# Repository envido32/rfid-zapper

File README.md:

# RFID Zapper

RFID Zapper sirve para quemar, dejando fuera de funcionamiento de forma irreversible los chips tipo RFID como el que se encuentran en llaves de puertas electronicas, [tarjetas de transporte público](https://www.sube.gob.ar/), [pasaportes](https://www.digitalcourage.de/), [boletas de voto electrónico](https://youtu.be/bJT6KLP6tWA), etc. No deja marca visible en absoluto ni emite ruido alguno. 

Este dispositivo debe utilizarse SOLO con fines didácticos o de pruebas. El mal uso del mismo **puede ocasionar serios daños en dispositivos electrónicos.**

**ATENCIÓN! Este dispositivo tiene una salida en ALTO VOLTAJE. Puede ocasionar daños en el organismo o incluso la muerte si se aplica la descarga sobre el cuerpo. Debe manipularse adecuadamente. No utilizar sin protección adecuada.**

## Licencia

RFID Zapper es un proyecto libre realizado por [*Manolo Envido*](https://twitter.com/Envido32), basado en el diseño presentado en la serie de videos de [*The Post Apocalyptic Inventor*](https://www.youtube.com/watch?v=E_Nsf0uU8IY&list=PLxaGnte1Dq0my2dtPL5y8sPR7xYXRrOCb).

Libre para utilizar, modificar, compartir y demás bajo los términos de la licencia [CERN Open Hardware Licence v1.2](LICENSE).

## Principio de funcionamiento

Se trata de un circuito elevador de tensión alimentado por una batería alcalina de 9v. Este elevador carga el capacitor y luego al cerrar el segundo interruptor se descarga el capacitor a través de la antena RFID. Esto genera un pulso electromagnético que al ser captado por un chip RFID lo utilizara como alimentación. Al ser un pulso de alta intensidad (y corta duración) la energía absorbida por el chip sera más alta que la soportada por el integrado probocándole un daño irreparable de forma totalmente silenciosa e invisible.

El circuito elevador de tensión es del tipo [boost](https://en.wikipedia.org/wiki/Boost_converter) alimentado por una [batería alcalina de 9v](https://en.wikipedia.org/wiki/Nine-volt_battery). Este circuito es controlado por un [PWM](https://en.wikipedia.org/wiki/Pulse-width_modulation) básico realizado con el [Timer 555](https://en.wikipedia.org/wiki/555_timer_IC) y controlado por el potenciómetro, se recomienda evitar un ciclo de trabajo del PWM mayor al 50% para evitar daños a la batería. Una vez cargado el capacitor el circuito de feedback enciende el LED y desactiva el Timer 555.

## Lite Edition

Menos componentes, más compacto. 

***Made with KiCAD***

***Order in PCBWay***

## Lista de materiales

Description | Part | References | Value | Footprint | Quantity Per PCB
---- | ---- | ---- | ---- | ---- | ---- 
Bornier | 2x1 | SW_SPST1 SW_SPST2 BT1 | SW_CHARGE SW_ZAP Baterry9v | Bornier | 3
Switch | DPDT | SW_SPST1 SW_SPST2 | SW_CHARGE SW_ZAP | Bornier | 1
Battery Cell | Baterry9v | BT1 | Alkaline 9v | Bornier | 1
Timer 555 IC | NE555 | U1 | NE555 | DIP 8 W7.62mm | 1
Capacitor | Ceramic | C1 | 100nF | Disc 4.3mm W1.9mm P5.00mm | 1
Capacitor | Ceramic | C2 | 10nF | Disc 4.3mm W1.9mm P5.00mm | 1
Capacitor | Polarised | C3 | 120uF 400v | Radial D18.0mm P7.50mm | 1
LED | Generic | DL1 | Any colour | LED 3.0mm | 1
Diode | Ultra Fast Recovery Rectifier | D3 | RG4 | P10.16mm | 1
Diode | Generic | D1 D2 | 1N4148 | P10.16mm | 2
Diode | Zenner v5.1 | DZ1 | 1N4733A | P10.16mm | 1
PowerMESH MOSFET | N-CHANNEL 900V 4ohm 3.5 A | Q2 | P3NB90 FP IRF3205| TO-220 | 1
Inductor | With Iron Core | L1 | 100uH | Toroid 5x10mm | 1
Small Signal Transistor | NPN 45V Vce 0.1A Ic | Q1 | BC549 | TO-92 | 1
Resistor | Generic | R1 R6 | 330ohm 1/8w | L3.6mm D1.6mm P7.62mm | 2
Resistor | Generic | R3 R9 | 150kohm 1/8w | L3.6mm D1.6mm P7.62mm | 2
Resistor | Generic | R8 | 10Mohm 1/8w | L3.6mm D1.6mm P7.62mm | 1
Potentionmeter | Trimmer | R2 | 500kohm 1/8w | POT | 1

Costo de los materiales total aproximado (a Septiembre 2017, argentina): 
*10 U$D*

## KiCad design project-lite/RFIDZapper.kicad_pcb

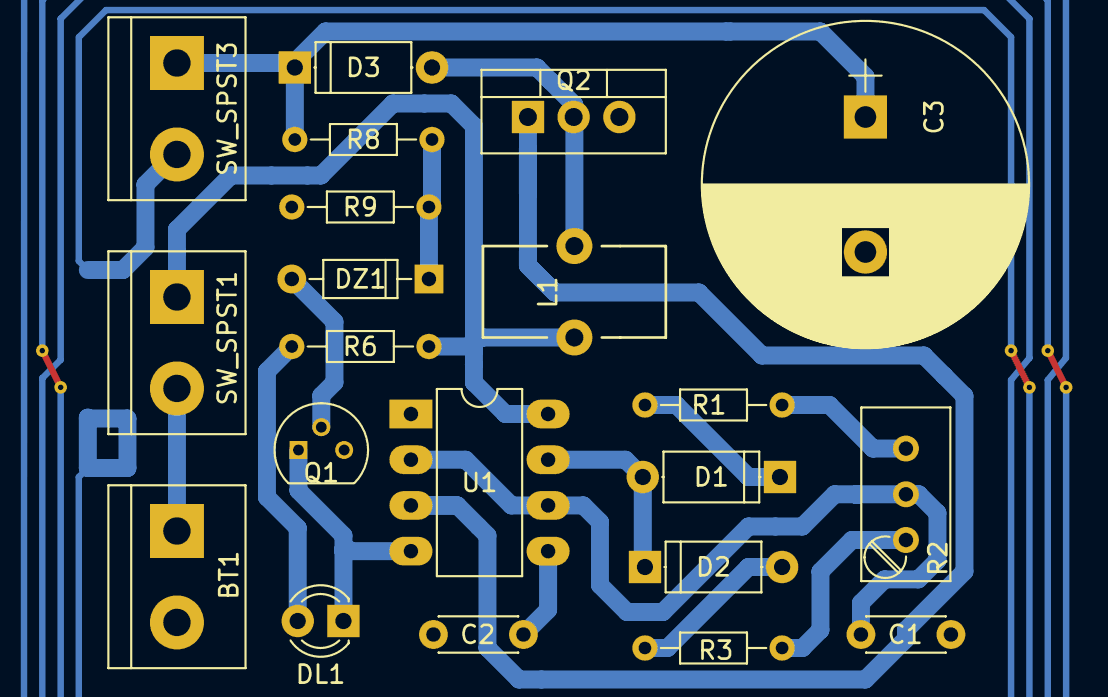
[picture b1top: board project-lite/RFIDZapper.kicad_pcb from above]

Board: 2 copper layers, 22 parts (1 on the bottom side), 18 nets.

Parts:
AE1: Antenna_RFID; NFC_ANTENNA2_INSIDE_CONNECTION
BT1: Battery9v; bornier2
C1: 100nF; C_Disc_D4.3mm_W1.9mm_P5.00mm
C2: 10nF; C_Disc_D4.3mm_W1.9mm_P5.00mm
C3: 120uF 400v; CP_Radial_D18.0mm_P7.50mm
D1, D2: 1N4148; D_A-405_P7.62mm_Horizontal
D3: RG4; D_A-405_P7.62mm_Horizontal
DL1: LED; LED_D3.0mm
DZ1: 5.1v; D_DO-35_SOD27_P7.62mm_Horizontal
L1: 100uH; Choke_Toroid_5x10mm_Vertical
Q1: BC549; TO-92_Molded_Narrow
Q2: P3NB90 FP; TO-220_Vertical
R1, R6: 330; R_Axial_DIN0204_L3.6mm_D1.6mm_P7.62mm_Horizontal
R2: 500k; Potentiometer_Trimmer_Bourns_3296W
R3, R9: 150k; R_Axial_DIN0204_L3.6mm_D1.6mm_P7.62mm_Horizontal
R8: 10M; R_Axial_DIN0204_L3.6mm_D1.6mm_P7.62mm_Horizontal
SW_SPST1: SW_CHARGE; bornier2
SW_SPST3: SW_ZAP; bornier2
U1: NE555; DIP-8_W7.62mm_LongPads

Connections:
/CV: C2.1, U1.5
/DIS: D1.2, D2.1, U1.7
/THR: C1.2, R2.2, U1.2, U1.6
/VCC: BT1.1, SW_SPST1.2
/VHI: C3.1, D3.1, R8.1, SW_SPST3.1
/VLO: L1.1, R6.1, SW_SPST1.1, U1.8
GNDPWR: AE1.2, BT1.2, C1.1, C2.2, C3.2, Q1.3, Q2.3, R9.2, U1.1
unnamed: AE1.1, SW_SPST3.2
unnamed: D1.1, R1.1
unnamed: D2.2, R3.1
unnamed: D3.2, L1.2, Q2.2
unnamed: DL1.2, R6.2
unnamed: DZ1.1, R8.2, R9.1
unnamed: DZ1.2, Q1.2
unnamed: R1.2, R2.3
unnamed: R2.1, R3.2
PWM: Q2.1, U1.3
RST: DL1.1, Q1.1, U1.4

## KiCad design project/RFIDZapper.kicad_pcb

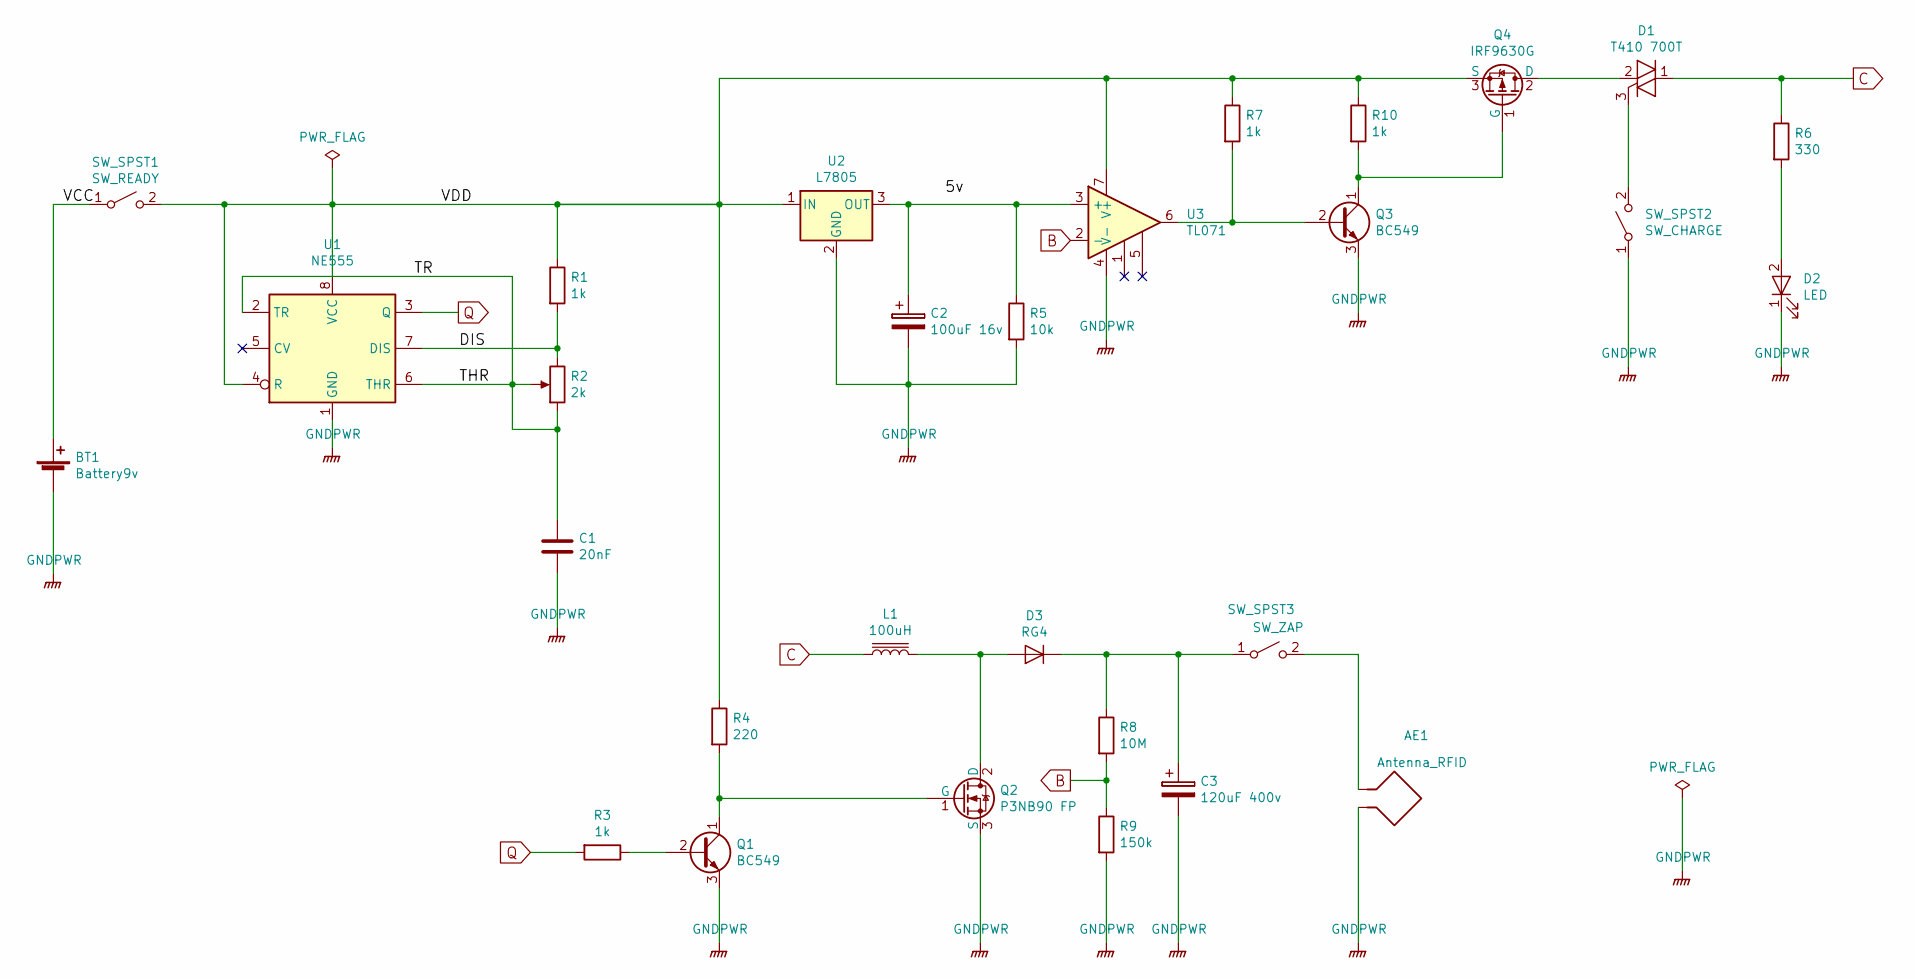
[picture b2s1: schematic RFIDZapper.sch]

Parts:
AE1: Antenna_RFID; NFC_ANTENNA_40_40
BT1: Battery9v; bornier2
C1: 20nF; C_Disc_D4.3mm_W1.9mm_P5.00mm
C2: 100uF 16v; CP_Radial_D4.0mm_P2.00mm
C3: 120uF 400v; CP_Radial_D18.0mm_P7.50mm
D1: T410 700T; TO-220_Horizontal
D2: LED; LED_D3.0mm
D3: RG4; D_A-405_P10.16mm_Horizontal
L1: 100uH; Choke_Toroid_5x10mm_Vertical
Q1, Q3: BC549; TO-92_Molded_Narrow
Q2: P3NB90 FP; TO-220_Horizontal
Q4: IRF9630G; TO-220_Horizontal
R1, R3, R7, R10: 1k; R_Axial_DIN0204_L3.6mm_D1.6mm_P7.62mm_Horizontal
R2: 2k; Potentiometer_Trimmer_Bourns_3296W
R4: 220; R_Axial_DIN0204_L3.6mm_D1.6mm_P7.62mm_Horizontal
R5: 10k; R_Axial_DIN0204_L3.6mm_D1.6mm_P7.62mm_Horizontal
R6: 330; R_Axial_DIN0204_L3.6mm_D1.6mm_P7.62mm_Horizontal
R8: 10M; R_Axial_DIN0204_L3.6mm_D1.6mm_P7.62mm_Horizontal
R9: 150k; R_Axial_DIN0204_L3.6mm_D1.6mm_P7.62mm_Horizontal
SW_SPST1: SW_READY; bornier2
SW_SPST2: SW_CHARGE; bornier2
SW_SPST3: SW_ZAP; bornier2
U1: NE555; DIP-8_W7.62mm_LongPads
U2: L7805; TO-220_Horizontal
U3: TL071; DIP-8_W7.62mm_LongPads

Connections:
/DIS: R1.2, R2.3, U1.7 (DIS)
/THR: C1.1, R2.1, R2.2, U1.2 (TR), U1.6 (THR)
/VCC: BT1.1 (+), SW_SPST1.1 (A)
/VDD: Q4.3 (S), R1.1, R4.1, R7.1, R10.1, SW_SPST1.2 (B), U1.4 (R), U1.8 (VCC), U2.1 (IN), U3.7 (V+)
A: Q1.1 (C), Q2.1 (G), R4.2
B: R8.2, R9.1, U3.2 (-)
C: D1.2 (A2), Q4.2 (D)
GNDPWR: AE1.2, BT1.2 (-), C1.2, C2.2, C3.2, D2.1 (K), Q1.3 (E), Q2.3 (S), Q3.3 (E), R5.2, R9.2, SW_SPST2.1 (A), U1.1 (GND), U2.2 (GND), U3.4 (V-)
unnamed: AE1.1, SW_SPST3.2 (B)
unnamed: C2.1, R5.1, U2.3 (OUT), U3.3 (+)
unnamed: C3.1, D3.1 (K), R8.1, SW_SPST3.1 (A)
unnamed: D1.1 (A1), L1.1, R6.1
unnamed: D1.3 (G), SW_SPST2.2 (B)
unnamed: D2.2 (A), R6.2
unnamed: D3.2 (A), L1.2, Q2.2 (D)
unnamed: Q1.2 (B), R3.1
unnamed: Q3.1 (C), Q4.1 (G), R10.2
unnamed: Q3.2 (B), R7.2, U3.6
Q: R3.2, U1.3 (Q)

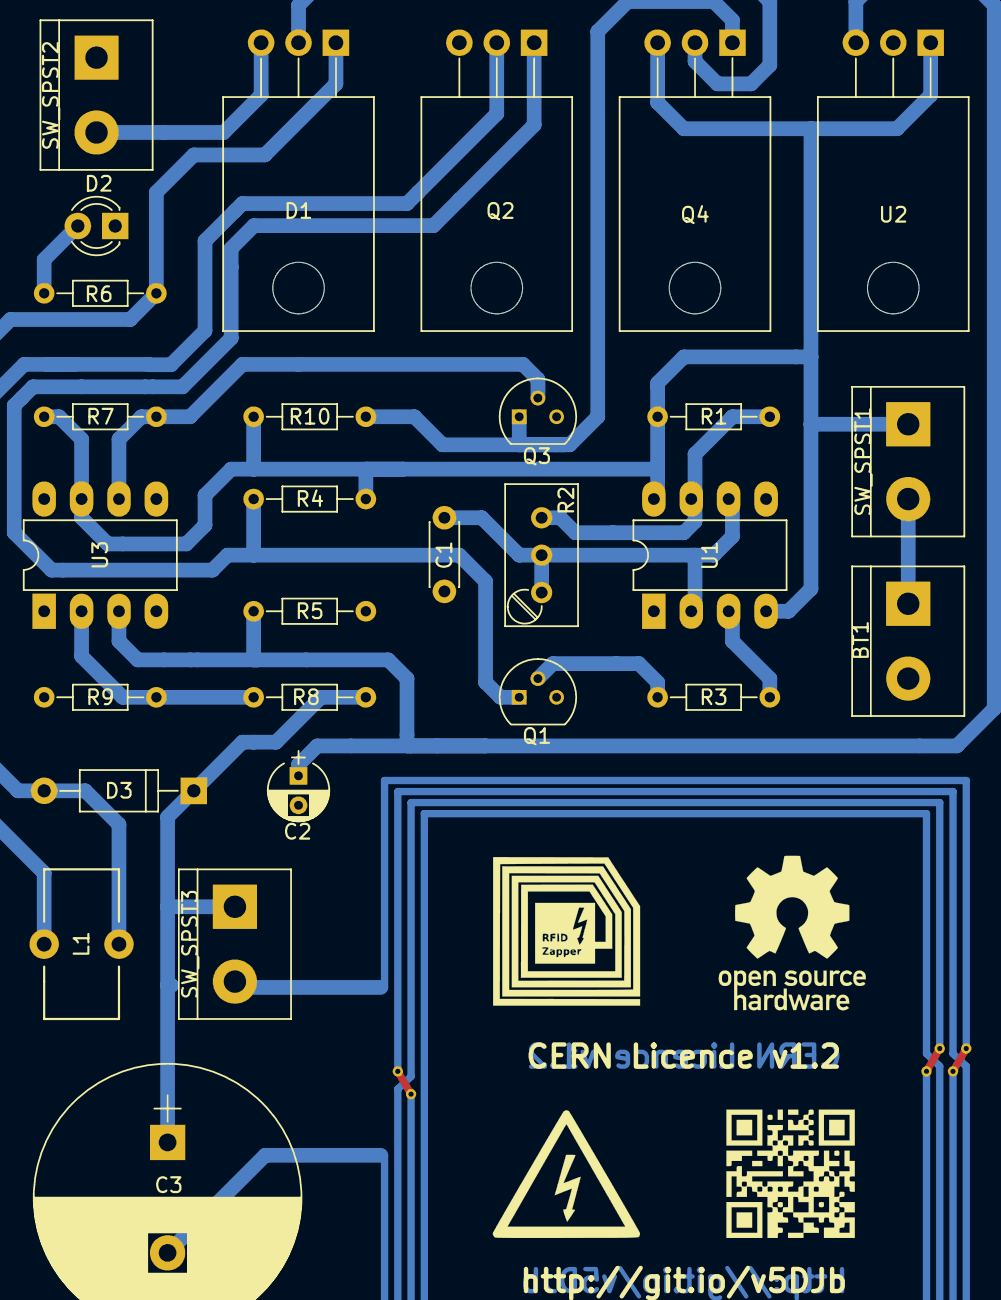
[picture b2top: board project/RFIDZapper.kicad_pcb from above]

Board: 2 copper layers, 29 parts (1 on the bottom side), 19 nets.

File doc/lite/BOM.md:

## RFIF Zapper ( http://git.io/v5DJb ) 

## Lista de materiales

Description | Part | References | Value | Footprint | Quantity Per PCB
---- | ---- | ---- | ---- | ---- | ---- 
single battery cell | Battery_Cell | BT1 | Battery9v | bornier2 | 1
Polarised capacitor | CP | C2 | 100uF 16v | CP_Radial_D4.0mm_P2.00mm | 1
Polarised capacitor | CP | C3 | 120uF 400v | CP_Radial_D18.0mm_P7.50mm | 1
Unpolarized capacitor | C | C1 | 20nF | C_Disc_D4.3mm_W1.9mm_P5.00mm | 1
LED generic | LED | D2 | LED | LED_D3.0mm | 1
Diode | D | D3 | RG4 | D_A-405_P10.16mm_Horizontal | 1
triode for alternating current (TRIAC) | Q_TRIAC_AAG | D1 | T410 700T | TO-220_Horizontal | 1
Inductor with Iron Core | L_Core_Iron | L1 | 100uH | Choke_Toroid_5x10mm_Vertical | 1
45V Vce, 0.1A Ic, NPN, Small Signal Transistor, TO-92 | BC549 | Q1 Q3 | BC549 | TO-92_Molded_Narrow | 2
6.5A, 200V, 0.800 Ohm, P-Channel Power MOSFET | IRF9540N-RESCUE-RFIDZapper | Q4 | IRF9630G | TO-220_Horizontal | 1
N - CHANNEL 900V - 4 ohm - 3.5 A PowerMESH MOSFET | IRF3205 | Q2 | P3NB90 FP | TO-220_Horizontal | 1
Resistor | R | R8 | 10M | R_Axial_DIN0204_L3.6mm_D1.6mm_P7.62mm_Horizontal | 1
Resistor | R | R5 | 10k | R_Axial_DIN0204_L3.6mm_D1.6mm_P7.62mm_Horizontal | 1
Resistor | R | R9 | 150k | R_Axial_DIN0204_L3.6mm_D1.6mm_P7.62mm_Horizontal | 1
Resistor | R | R1 R3 R7 R10 | 1k | R_Axial_DIN0204_L3.6mm_D1.6mm_P7.62mm_Horizontal | 4
Resistor | R | R4 | 220 | R_Axial_DIN0204_L3.6mm_D1.6mm_P7.62mm_Horizontal | 1
Potentionmeter | POT | R2 | 2k | Potentiometer_Trimmer_Bourns_3266Y | 1
Resistor | R | R6 | 330 | R_Axial_DIN0204_L3.6mm_D1.6mm_P7.62mm_Horizontal | 1
Switch | SW_SPST | SW_SPST2 | SW_CHARGE | bornier2 | 1
Switch | SW_SPST | SW_SPST1 | SW_READY | bornier2 | 1
Switch | SW_SPST | SW_SPST3 | SW_ZAP | bornier2 | 1
5V Voltage regulator | L7805 | U2 | L7805 | TO-220_Horizontal | 1
555-series timer IC | NE555 | U1 | NE555 | DIP-8_W7.62mm_LongPads | 1
Low-Noise JFET-Input Operational Amplifier | TL071-RESCUE-RFIDZapper | U3 | TL071 | DIP-8_W7.62mm_LongPads | 1

Las resistencias son todas de 1/8W o 1/4W. Las llaves/switches y la batería se conectan con borneras o pines. Es recomendable incorporar un pequeño disipador al Q2 (P3NB90).

## Licencia

![Open Source Hardware](doc/open-source-hardware.png)

RFID Zapper es un proyecto libre realizado por [*Manolo Envido*](https://twitter.com/Envido32), basado en el diseño presentado en esta serie de videos: 

*The Post Apocalyptic Inventor* 

https://www.youtube.com/watch?v=E_Nsf0uU8IY&list=PLxaGnte1Dq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

Libre para utilizar, modificar, compartir y demás bajo los términos de la licencia [CERN Open Hardware Licence v1.2](LICENSE).

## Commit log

2017-09-12 Add CERN OHL v1.2 LICENSE
2017-09-12 Add details to README
    Reorder project files.
2017-09-13 Added logos
2017-09-14 Better 3D
2017-09-17 Lite imgs
2017-09-17 Lite edition
2017-09-17 Added Lite edition info
2017-09-17 Lite routed
2017-09-17 Minor logos update
2017-09-21 New Lite
2017-09-21 Cap rotated
2017-09-21 Licence and Lite on top
2017-09-21 Agragados los principios de funcionamiento
2017-09-21 Added some Wiki links
2017-09-21 Lite edition parts lists
2017-09-21 Fixed minnor errors
2017-09-21 Added some links
2017-09-21 Minor fixes
2017-09-22 Added details
2017-09-23 Gerber RS-247x with gerbV
2017-09-23 Added Bill of Materials
2017-09-23 PCBWay link
2017-09-24 Added Panflet (es)
2017-09-24 Added poster
2017-09-24 Set theme jekyll-theme-slate
2017-09-24 Rename README.md to README.old.md
2017-09-24 Added KiCAD logo
2017-09-24 Made with KiCAD
2017-09-26 Added prices
2018-08-28 Deleted duplicated
2021-11-09 Update README.md
    https://forum.kicad.info/t/warning-avoid-all-links-to-kicad-pcb-org-use-kicad-org/31521
